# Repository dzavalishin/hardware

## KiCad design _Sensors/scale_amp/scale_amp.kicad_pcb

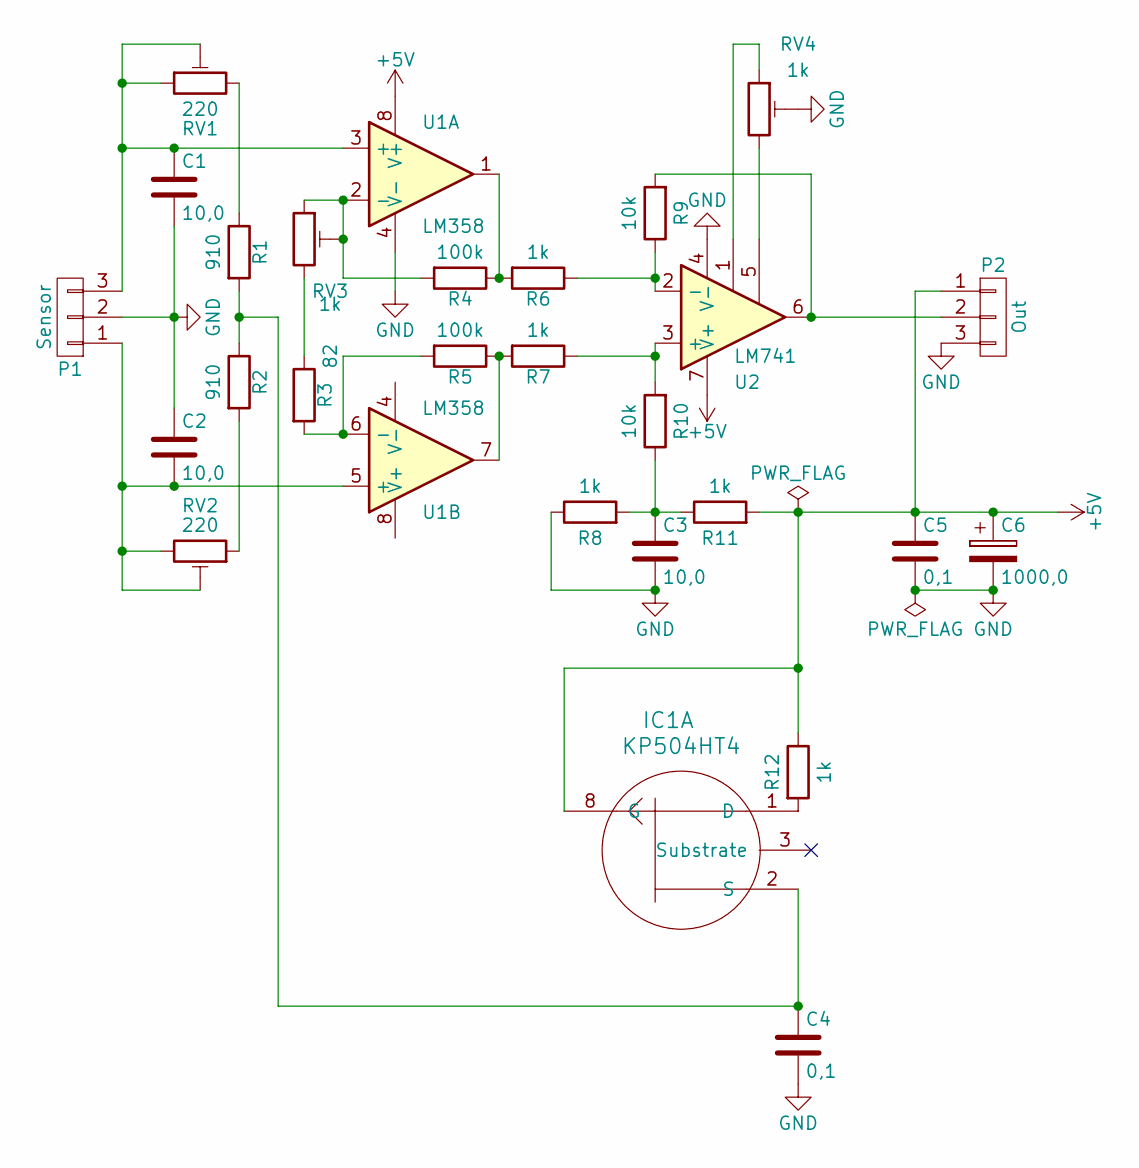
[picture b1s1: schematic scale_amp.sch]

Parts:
C1, C2, C3: 10,0; C_0805_HandSoldering
C4, C5: 0,1; C_1206_HandSoldering
C6: 1000,0; CP_Radial_Tantal_D10.5mm_P5.00mm
IC1: КР504НТ4; DIP-8_W7.62mm_Socket_LongPads
P1: Sensor; PINHEAD1-3
P2: Out; PINHEAD1-3
R1, R2: 910; R_0805_HandSoldering
R3: 82; R_0805_HandSoldering
R4, R5: 100k; R_0805_HandSoldering
R6, R7, R8, R11, R12: 1k; R_0805_HandSoldering
R9, R10: 10k; R_0805_HandSoldering
RV1, RV2: 220; Potentiometer_Trimmer_Suntan_TSR-3386C_Vertical
RV3, RV4: 1k; Potentiometer_Trimmer_Suntan_TSR-3386C_Vertical
U1: LM358; SOIC-8_3.9x4.9mm_Pitch1.27mm
U2: LM741; DIP-8_W7.62mm

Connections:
+5V: C5.1, C6.1, IC1.8 (G), P2.1, R11.2, R12.1, U1.8 (V+), U2.7 (V+)
GND: C1.2, C2.1, C3.2, C4.2, C5.2, C6.2, P1.2, P2.3, R8.1, RV4.2, U1.4 (V-), U2.4 (V-)
unnamed: C1.1, P1.3, RV1.1, RV1.2, U1.3 (+)
unnamed: C2.2, P1.1, RV2.2, RV2.3, U1.5 (+)
unnamed: C3.1, R8.2, R10.1, R11.1
unnamed: C4.1, IC1.2 (S), R1.2, R2.1
unnamed: IC1.1 (D), R12.2
unnamed: P2.2, R9.2, U2.6
unnamed: R1.1, RV1.3
unnamed: R2.2, RV2.1
unnamed: R3.1, RV3.3
unnamed: R3.2, R5.2, U1.6 (-)
unnamed: R4.1, R6.2, U1.1
unnamed: R4.2, RV3.1, RV3.2, U1.2 (-)
unnamed: R5.1, R7.2, U1.7
unnamed: R6.1, R9.1, U2.2 (-)
unnamed: R7.1, R10.2, U2.3 (+)
unnamed: RV4.1, U2.1
unnamed: RV4.3, U2.5

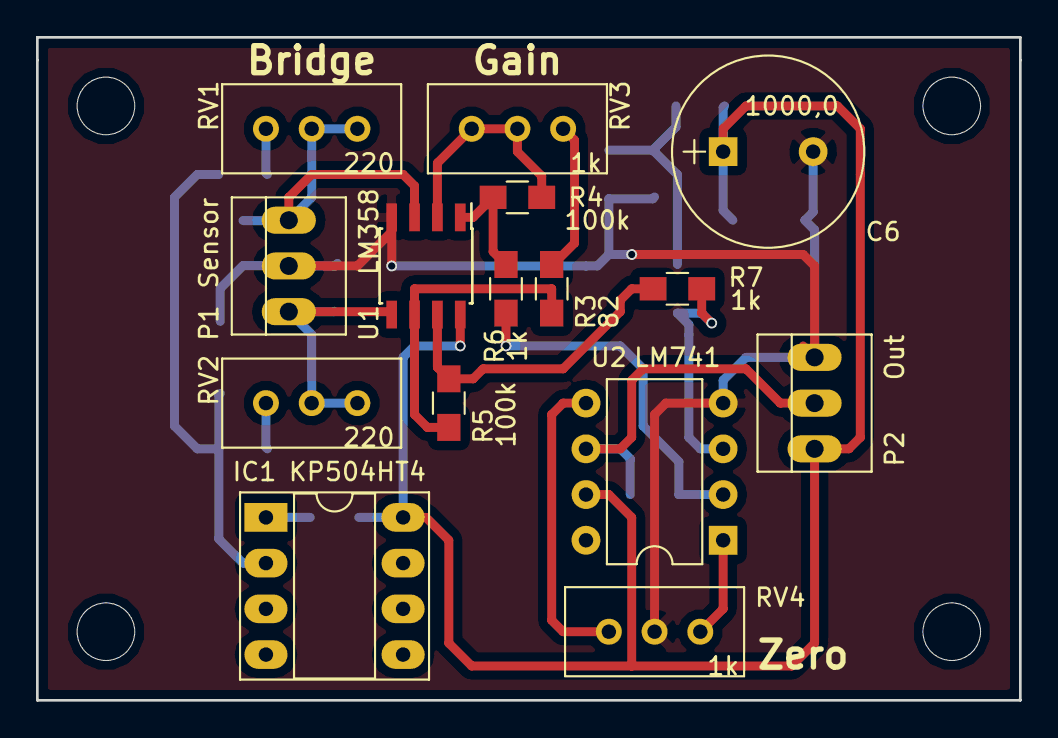
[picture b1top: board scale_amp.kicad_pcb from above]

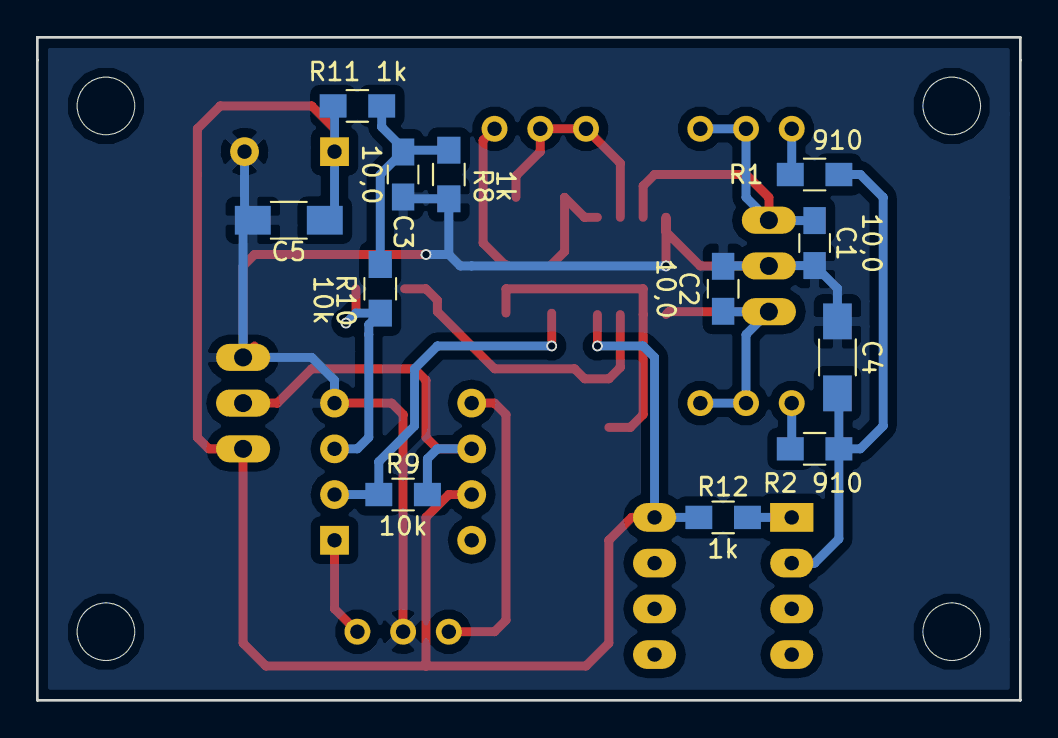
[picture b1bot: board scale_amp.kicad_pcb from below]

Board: 2 copper layers, 54.6 x 36.8 mm, 31 parts (12 on the bottom side), 19 nets.

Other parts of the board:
Hole: Hole; MountingHole_3.2mm_M3
Hole#2, Hole#3, Hole#4: Hole; MountingHole_3.2mm_M3

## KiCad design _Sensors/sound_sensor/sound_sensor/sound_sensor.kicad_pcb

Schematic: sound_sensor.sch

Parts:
C1, C4, C5, C9, C12, C17, C20, C21, C22: 0,1; C_1206_HandSoldering
C2, C16, C19, C23, C24, C27: 100,0; CP_Elec_6.3x5.3
C3, C8, C13, C14, C18: 10,0; C_0805_HandSoldering
C6: 33,0; CP_Elec_6.3x5.3
C7, C15: 470; C_0805_HandSoldering
C10: 0,047; C_0805_HandSoldering
C11: 0,022; C_0805_HandSoldering
C25, C26: 0,33; C_1206_HandSoldering
D1: 157УП2; DIP-14_W7.62mm_Socket_LongPads
D2, D3: 1n4148; D_MiniMELF_Handsoldering
D4: LED_BGRA; LED_Cree-PLCC4_3.2x2.8mm_CCW
J1: OutL; PinHeader_1x02_P2.54mm_Vertical
J2: InL; PinHeader_1x02_P2.54mm_Vertical
J3: InR; PinHeader_1x02_P2.54mm_Vertical
J4: Level; PinHeader_1x02_P2.54mm_Vertical
J5: OutR; PinHeader_1x02_P2.54mm_Vertical
J6: +24; PinHeader_1x02_P2.54mm_Vertical
JP1: Link; SolderJumper-2_P1.3mm_Bridged_Pad1.0x1.5mm
JP2: PwrL; SolderJumper-2_P1.3mm_Open_Pad1.0x1.5mm
JP3: PwrR; SolderJumper-2_P1.3mm_Bridged_Pad1.0x1.5mm
MH1, MH2, MH3, MH4: -; MountingHole_3.2mm_M3
Q1: MMBT3904; SOT-23
R1, R29: 22k; R_1206_HandSoldering
R2, R28: 100k; R_1206_HandSoldering
R3, R11, R18, R27: 47k; R_1206_HandSoldering
R4, R13, R30, R33: 1k; R_1206_HandSoldering
R5, R8, R9, R20, R21, R26: 200k; R_1206_HandSoldering
R6, R19, R23, R24, R25: 20k; R_1206_HandSoldering
R7, R22: 390k; R_1206_HandSoldering
R10, R16: 16k; R_1206_HandSoldering
R12, R15, R17: 100; R_1206_HandSoldering
R14: 10k; R_1206_HandSoldering
R31, R32: 2,2k; R_1206_HandSoldering
R34, R35: 56; R_Axial_DIN0516_L15.5mm_D5.0mm_P20.32mm_Horizontal
RV1, RV2: 1m; Potentiometer_Triwood_RM-065
RV3, RV4: 10k; Potentiometer_Triwood_RM-065
U1: LM2904; DIP-8_W7.62mm_Socket_LongPads
U2: LM2903; DIP-8_W7.62mm_Socket_LongPads
U3: L78L12; TO-92_Inline

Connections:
+12V: C21.1, C22.1, C26.2, C27.1, D4.4, Q1.3 (C), R4.1, R13.1, RV3.1, RV4.3, U1.8, U2.8, U3.1 (VO)
/OutL: C3.2, D1.13, R12.1
/OutR: C18.2, D1.10, R15.2
/PrePwr: C12.1, C13.1, D1.11, Q1.2 (E), R23.2, R24.2, RV1.3, RV2.1
GND: C1.1, C5.2, C6.2, C7.1, C12.2, C13.2, C15.2, C16.2, C20.2, C21.2, C22.2, C23.2, C24.2, C25.2, C26.1, C27.2, D1.4, D1.5, J1.1, J2.2, J3.2, J4.1, J5.1, J6.2, R1.1, R6.1, R11.1, R14.2, R18.2, R19.2, R25.2, R29.2, R32.1, R33.1, RV3.3, RV4.1, U1.4, U2.4, U3.2 (GND)
unnamed: C1.2, R2.1, R3.1
unnamed: C2.1, D1.14, R1.2
unnamed: C2.2, R2.2
unnamed: C3.1, J1.2
unnamed: C4.1, R3.2, R5.2
unnamed: C4.2, D1.2, R7.1
unnamed: C5.1, C6.1, R4.2, R10.1, R33.2
unnamed: C7.2, C8.1, D1.3, R7.2, R11.2
unnamed: C8.2, J2.1, JP1.2, JP2.1
unnamed: C9.1, R16.2, U1.1, U1.2
unnamed: C9.2, R14.1, U1.5
unnamed: C10.1, C11.2, R16.1
unnamed: C10.2, R12.2, R15.1
unnamed: C11.1, R10.2, U1.3
unnamed: C14.1, C15.1, D1.6, R18.1, R22.2
unnamed: C14.2, J3.1, JP1.1, JP3.2
unnamed: C16.1, D2.1, R17.2, R19.1, U1.6, U2.2, U2.6
unnamed: C17.1, D1.7, R22.1
unnamed: C17.2, R26.1, R27.1
unnamed: C18.1, J5.2
unnamed: C19.1, D1.9, R29.1
unnamed: C19.2, R28.2
unnamed: C20.1, R27.2, R28.1
unnamed: C23.1, Q1.1 (B), R13.2
unnamed: C24.1, C25.1, R35.1, U3.3 (VI)
unnamed: D1.1, R5.1, R8.1
unnamed: D1.8, R20.1, R26.2
unnamed: D2.2, U1.7
unnamed: D3.1, R34.1
unnamed: D3.2, J6.1
unnamed: D4.1, R31.1
unnamed: D4.2, R30.1
unnamed: D4.3, R32.2
unnamed: J4.2, R17.1
unnamed: JP2.2, R23.1
unnamed: JP3.1, R24.1
unnamed: R6.2, R8.2, R9.1
unnamed: R9.2, RV1.1, RV1.2
unnamed: R20.2, R21.1, R25.1
unnamed: R21.2, RV2.2, RV2.3
unnamed: R30.2, U2.1
unnamed: R31.2, U2.7
unnamed: R34.2, R35.2
unnamed: RV3.2, U2.3
unnamed: RV4.2, U2.5

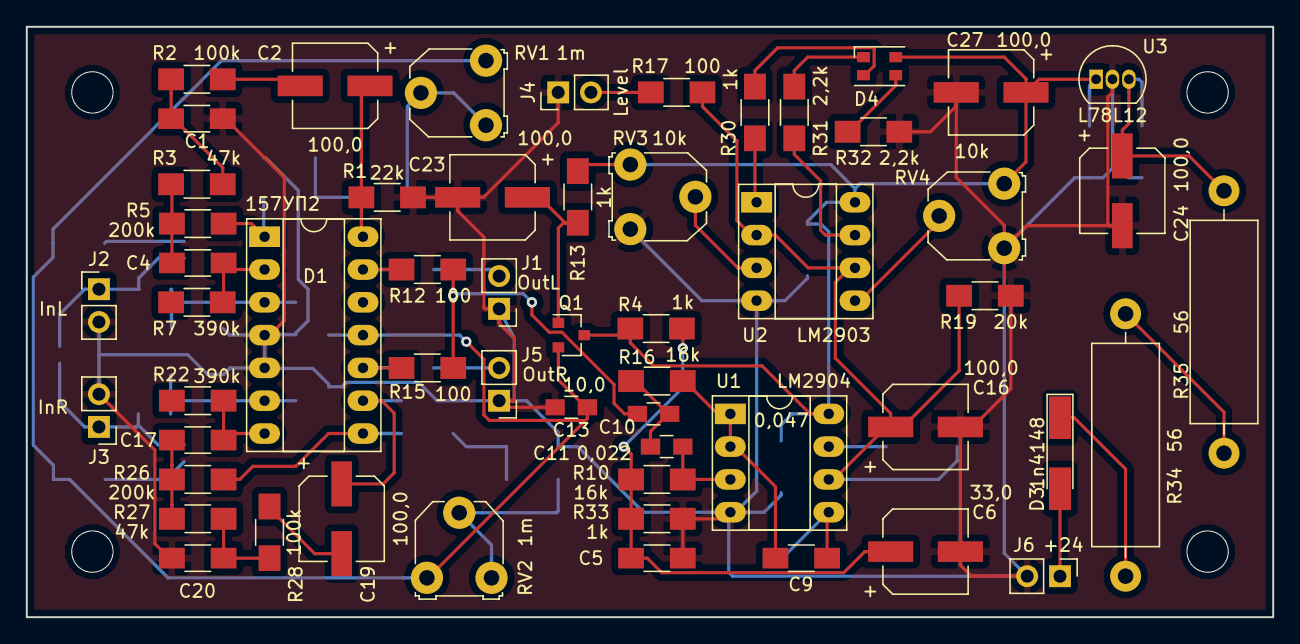
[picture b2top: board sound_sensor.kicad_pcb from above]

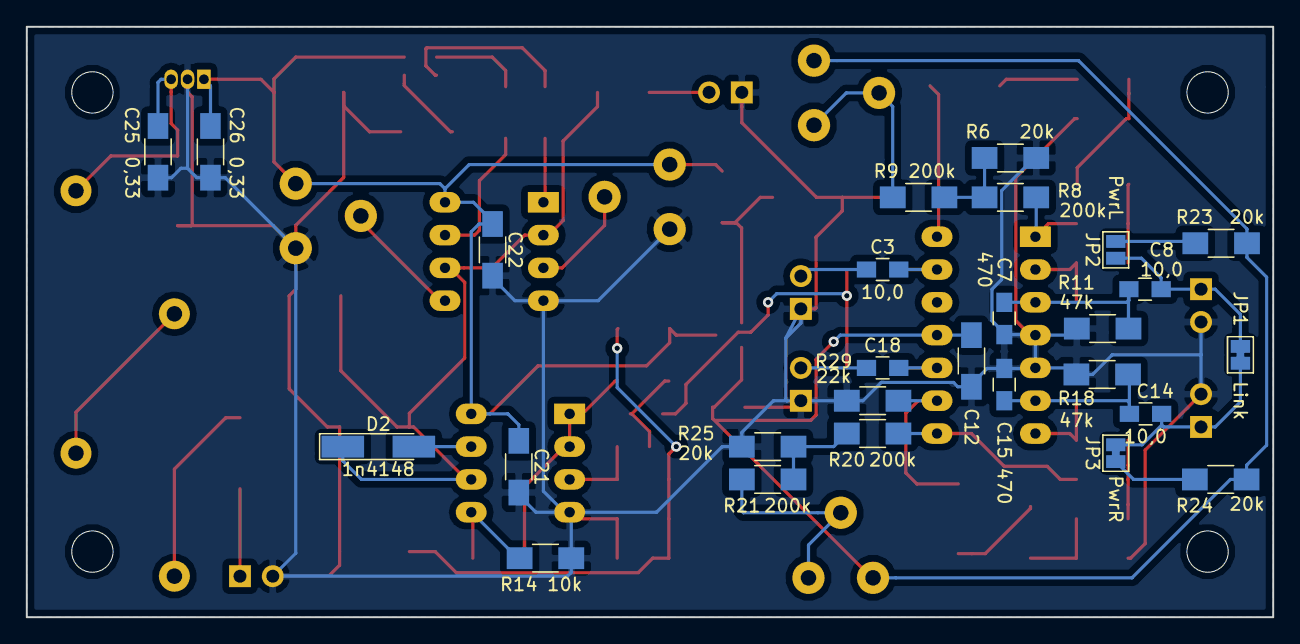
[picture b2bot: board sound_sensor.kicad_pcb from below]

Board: 2 copper layers, 96.5 x 45.7 mm, 87 parts (27 on the bottom side), 50 nets.

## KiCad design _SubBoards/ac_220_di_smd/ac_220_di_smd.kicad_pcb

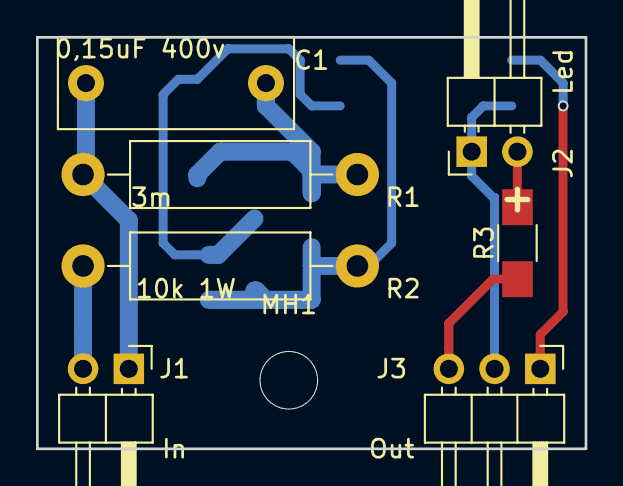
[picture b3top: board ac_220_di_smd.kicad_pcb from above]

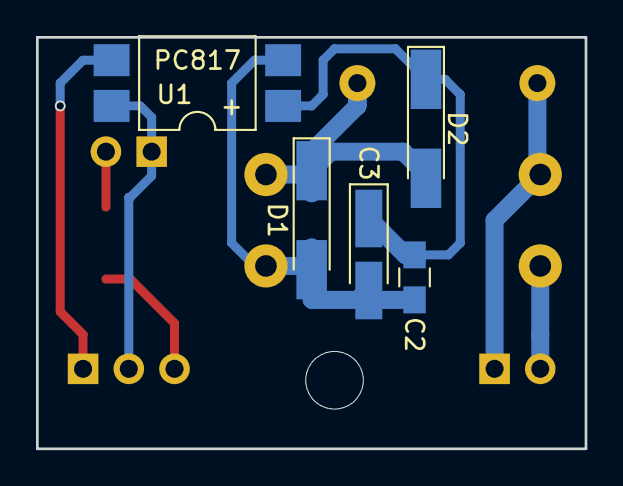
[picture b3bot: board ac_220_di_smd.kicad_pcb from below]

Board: 2 copper layers, 30.5 x 22.9 mm, 13 parts (5 on the bottom side), 9 nets.

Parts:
C1: 0,15uF 400v; C_Rect_L13.0mm_W5.0mm_P10.00mm_FKS3_FKP3_MKS4
C2: 0,1; C_0805_HandSoldering
C3: 10,0; CP_Tantalum_Case-A_EIA-3216-18_Hand
D1, D2: 4448; D_MiniMELF_Handsoldering
J1: In; Pin_Header_Angled_1x02_Pitch2.54mm
J2: Led; Pin_Header_Angled_1x02_Pitch2.54mm
J3: Out; Pin_Header_Angled_1x03_Pitch2.54mm
MH1: MountingHole; MountingHole_3.2mm_M3
R1: 3m; R_Axial_DIN0411_L9.9mm_D3.6mm_P15.24mm_Horizontal
R2: 10k 1W; R_Axial_DIN0411_L9.9mm_D3.6mm_P15.24mm_Horizontal
R3: 4,7k; R_1206_HandSoldering
U1: PC817; SMDIP-4_W9.53mm

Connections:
unnamed: C1.1, D1.1, D2.2, R1.1
unnamed: C1.2, J1.1, R1.2
unnamed: C2.1, C3.2, D1.2, R2.1, U1.2
unnamed: C2.2, C3.1, D2.1, U1.1
unnamed: J1.2, R2.2
unnamed: J2.1, J3.2, U1.4
unnamed: J2.2, R3.2
unnamed: J3.1, U1.3
unnamed: J3.3, R3.1

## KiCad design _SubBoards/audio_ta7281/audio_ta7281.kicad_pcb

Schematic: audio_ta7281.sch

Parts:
C1, C8, C9, C12: 100,0; CP_Radial_D6.3mm_P2.50mm
C2, C4: 1,0; CP_Radial_D5.0mm_P2.00mm
C3: 1n; C_1206_HandSoldering
C5: 47,0; CP_Radial_D8.0mm_P5.00mm
C6: 1000,0; CP_Radial_D12.5mm_P5.00mm
C7, C10: 0,1; C_1206_HandSoldering
C11, C14: 0,22; C_Disc_D4.3mm_W1.9mm_P5.00mm
C13: 0,15; C_Disc_D8.0mm_W5.0mm_P10.00mm
J1: PwrA; TerminalBlock_Pheonix_MKDS1.5-2pol
J2: PwrB; TerminalBlock_Pheonix_MKDS1.5-2pol
J3: Out; TerminalBlock_Pheonix_MKDS1.5-2pol
P1: In; PINHEAD1-2
R1, R2: 430; R_1206_HandSoldering
R3: 1; R_Axial_DIN0922_L20.0mm_D9.0mm_P30.48mm_Horizontal
R4: 2k; R_1206_HandSoldering
R5: 43; R_1206_HandSoldering
U1: TA7281; HZIP12-P-1.78B

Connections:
/In: C2.2, P1.2
/OutA: C8.2, C14.1, J3.2, R3.1, R4.1, U1.1
/OutB: C9.2, C11.2, C13.2, J3.1, U1.6
/Power: C6.1, C7.2, C11.1, J1.2, J2.2, U1.3
GNDA: C1.2, C4.2, C5.2, C6.2, C7.1, C10.2, C14.2, J1.1, J2.1, P1.1, R5.2, U1.4, U1.10
unnamed: C1.1, R1.2
unnamed: C2.1, C3.1, U1.12
unnamed: C3.2, R1.1, U1.11
unnamed: C4.1, U1.8
unnamed: C5.1, U1.7
unnamed: C8.1, U1.2
unnamed: C9.1, U1.5
unnamed: C10.1, C12.1, U1.9
unnamed: C12.2, R2.2
unnamed: C13.1, R3.2
unnamed: R2.1, R4.2, R5.1

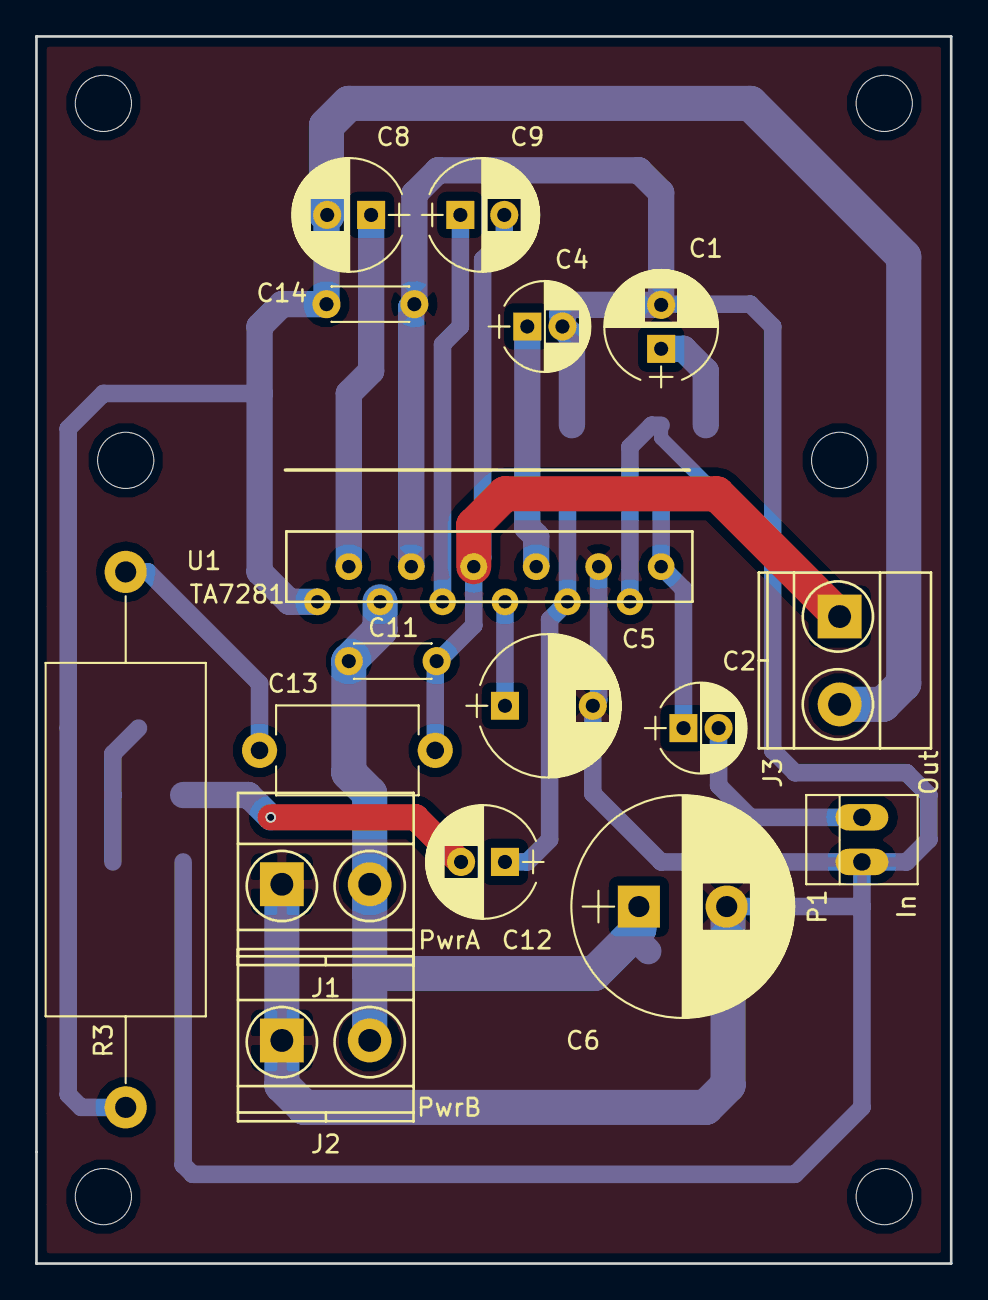
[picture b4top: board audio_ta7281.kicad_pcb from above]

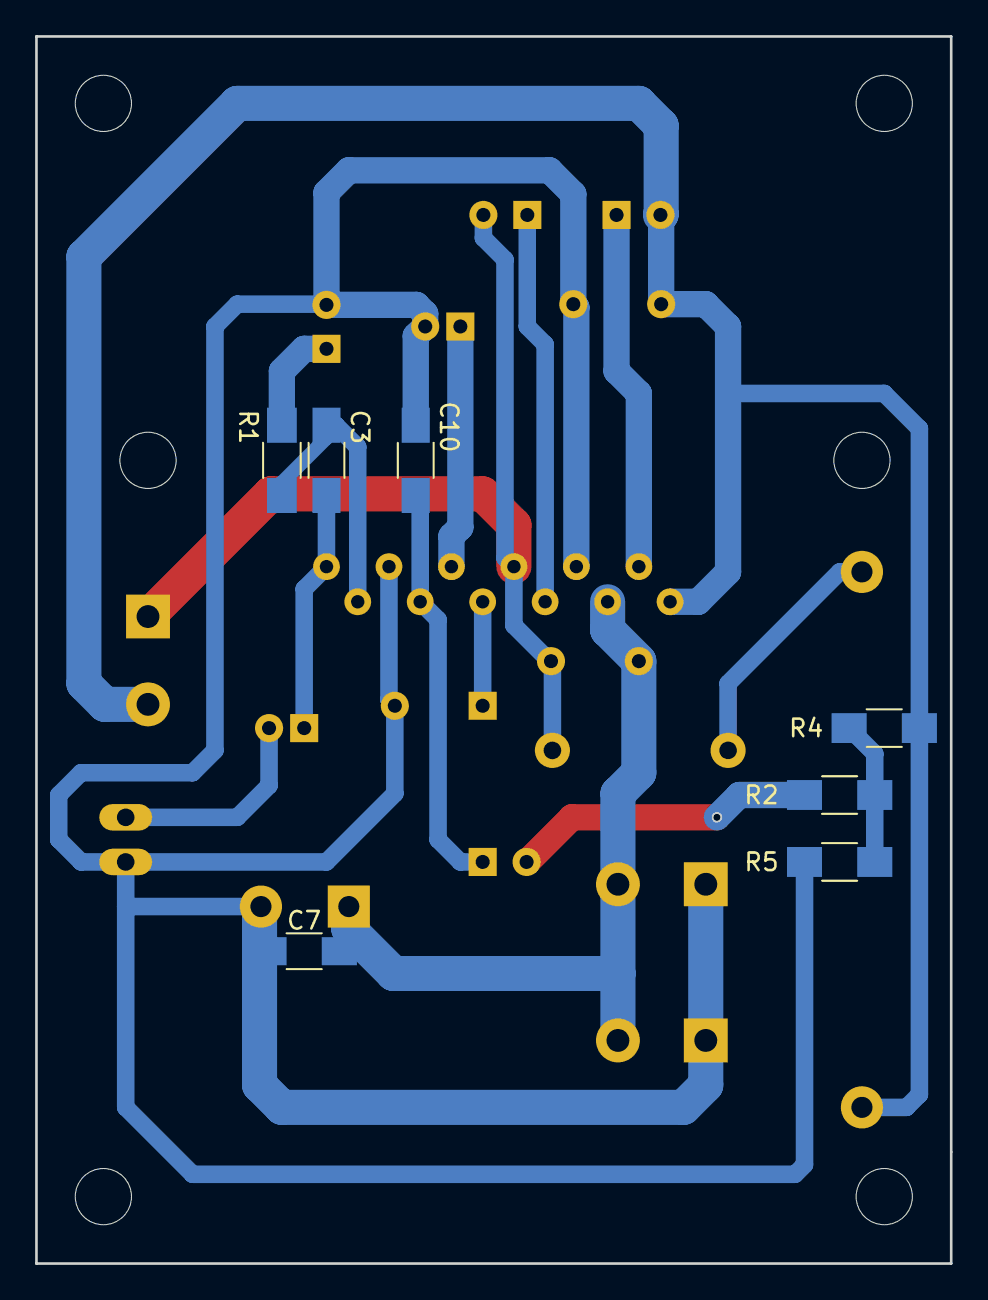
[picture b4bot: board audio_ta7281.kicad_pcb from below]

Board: 2 copper layers, 52.1 x 69.8 mm, 24 parts (7 on the bottom side), 16 nets.

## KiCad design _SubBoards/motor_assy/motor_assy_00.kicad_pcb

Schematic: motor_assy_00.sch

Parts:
C1, C9, C14: 47,0; CP_Elec_6.3x5.3
C2, C5, C7, C8, C10, C11, C12, C13: 0,1; C_1206_HandSoldering
C3: 1,0; C_1206_HandSoldering
C4, C6: 100,0; CP_Elec_6.3x5.3
D1: L293D; DIP-16_W7.62mm_Socket_LongPads
D2, D3, D4, D5, D6, D7, D8, D9, D11: D; D_MiniMELF_Handsoldering
D10: 15v0; D_MiniMELF_Handsoldering
J1: Ai_Ext; TerminalBlock_Pheonix_MKDS1.5-2pol
L1: 100mH; Choke_Toroid_8x16mm_Vertical
P1: Control; Socket_Strip_Angled_1x07
P2: Motor1; Socket_Strip_Angled_1x02
P3: Motor2; Socket_Strip_Angled_1x02
P4: +5/Sense; Socket_Strip_Angled_1x04
P5: +12; Socket_Strip_Angled_1x02
Q1: 2N3904; TO-92_Molded_Narrow
R1, R2: 10k; R_1206_HandSoldering
R3, R4: 100k; R_1206_HandSoldering
R5: 0,2; R_Axial_DIN0414_L11.9mm_D4.5mm_P15.24mm_Horizontal
R6, R7: 200; R_1206_HandSoldering
R8: 2k; R_1206_HandSoldering
R9: 1M; R_1206_HandSoldering
R10: 1k; R_1206_HandSoldering
R11: 100; R_1206_HandSoldering
U1: TL082; DIP-8_W7.62mm_Socket_LongPads
U2: L78L05; TO-92_Inline_Narrow_Oval

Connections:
+5V: C13.1, C14.2, D1.16 (VccDig), P4.2, R1.2, R2.2, U2.1 (VO)
+12V: C7.2, C9.1, C12.1, D10.1, R11.1, U1.8 (V+), U2.3 (VI)
/+12Motor: C4.1, C5.1, L1.2, R5.1, R6.2
/A1: D1.2 (A), P1.2
/A2: D1.10 (A), P1.6, R4.2
/Ai_Ext: P4.4, U1.6 (-), U1.7
/Ai_I_Sense: C3.1, P4.3, Q1.3, R8.1
/B1: D1.7 (B), P1.3
/B2: D1.15 (B), P1.5, R3.2
/En1: D1.1 (En), P1.1, R1.1
/En2: D1.9 (En), P1.7, R2.1
/MPower: C1.1, C2.1, D1.8 (Pwr), D2.1, D4.1, D6.1, D8.1, R5.2, R7.2
GND: C1.2, C2.2, C3.2, C4.2, C5.2, C6.2, C7.1, C8.2, C9.2, C12.2, C13.2, C14.1, D1.4 (Gnd), D1.5 (Gnd), D1.12 (Gnd), D1.13 (Gnd), D3.2, D5.2, D7.2, D9.2, D10.2, J1.2, P1.4, P4.1, P5.2, R3.1, R4.1, R8.2, R9.1, U1.4 (V-), U2.2 (GND)
unnamed: C6.1, C8.1, D11.1, L1.1, R11.2
unnamed: C10.1, D1.3 (OA), D2.2, D3.1, P2.1
unnamed: C10.2, D1.6 (OB), D6.2, D7.1, P2.2
unnamed: C11.1, D1.11 (OA), D4.2, D5.1, P3.1
unnamed: C11.2, D1.14 (OB), D8.2, D9.1, P3.2
unnamed: D11.2, P5.1
unnamed: J1.1, R9.2, R10.2
unnamed: Q1.1, R6.1, U1.3 (+)
unnamed: Q1.2, U1.1
unnamed: R7.1, U1.2 (-)
unnamed: R10.1, U1.5 (+)

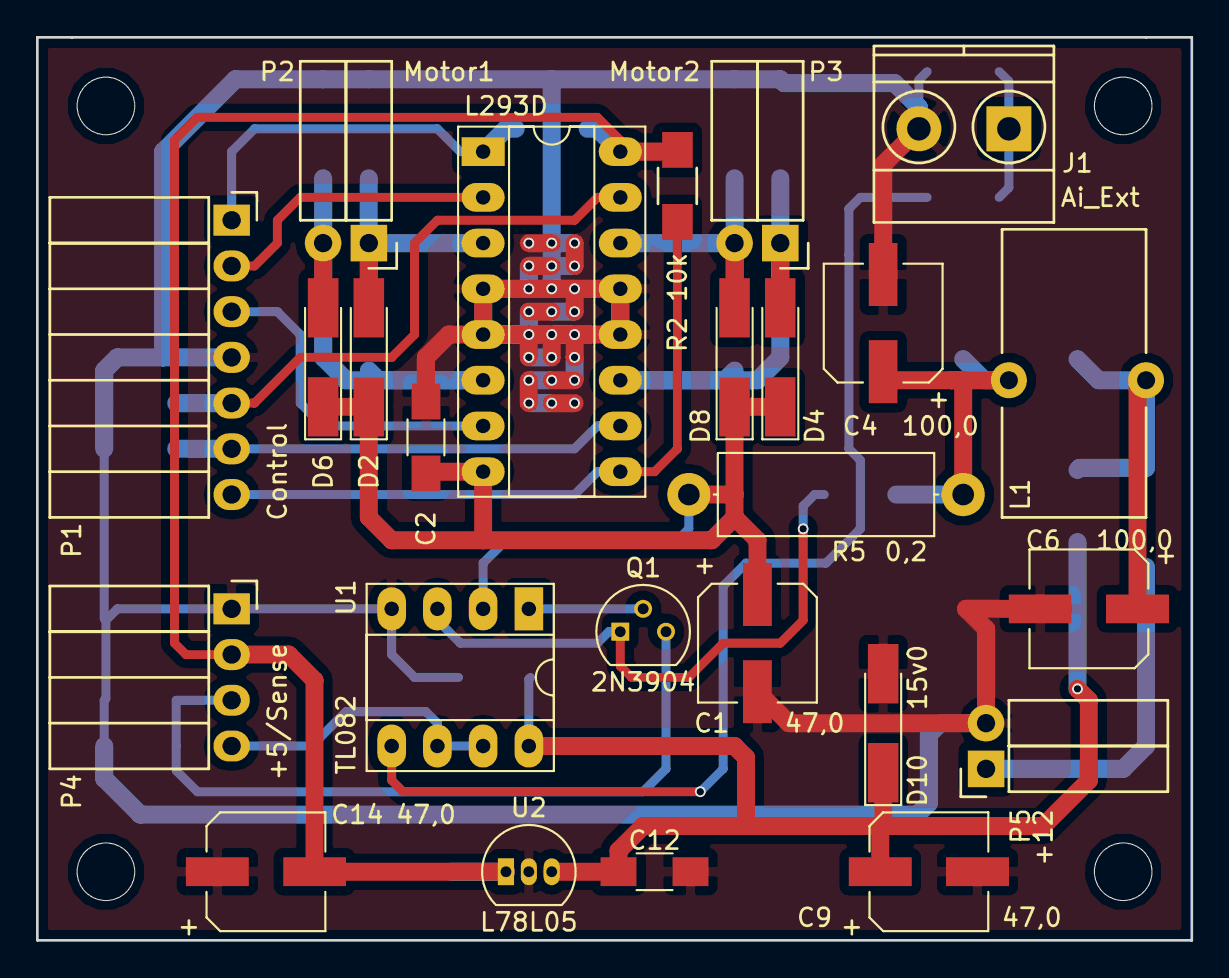
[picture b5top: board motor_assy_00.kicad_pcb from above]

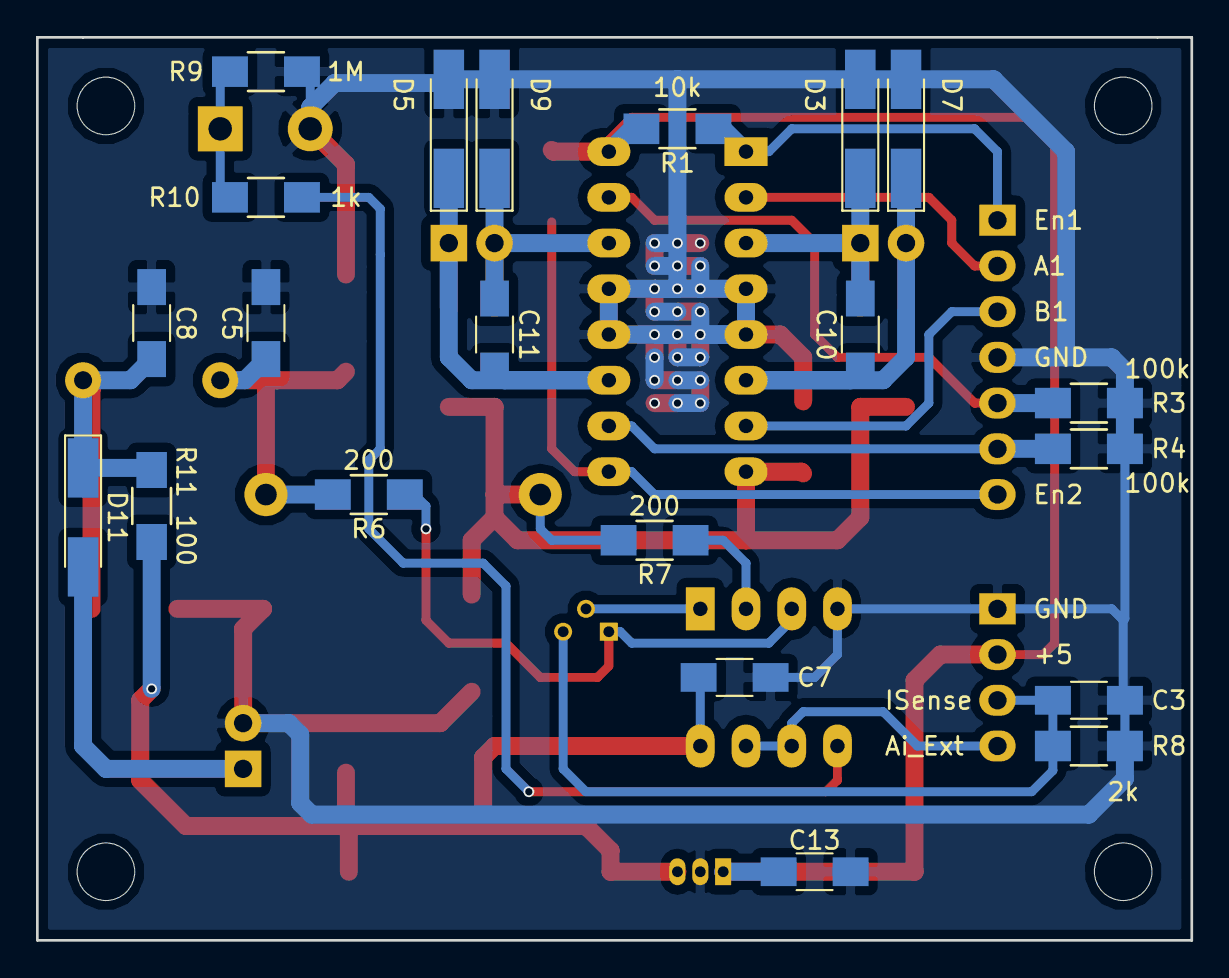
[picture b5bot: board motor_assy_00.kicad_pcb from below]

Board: 2 copper layers, 64.1 x 50.2 mm, 50 parts (21 on the bottom side), 24 nets.

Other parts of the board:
hole: MountingHole_3.2mm_M3
hole#2, hole#3, hole#4: MountingHole_3.2mm_M3

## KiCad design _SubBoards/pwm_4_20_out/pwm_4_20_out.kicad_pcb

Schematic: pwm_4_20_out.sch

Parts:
C1, C2: 10,0; C_0805_HandSoldering
IC1: КР504НТ4; DIP-8_W7.62mm_LongPads
J1, J3: Out 4-20 mA; TerminalBlock_bornier-2_P5.08mm
J2: PWM; Pin_Header_Angled_1x04_Pitch2.54mm
R1, R2: 560; R_0805_HandSoldering
R3, R4: 18; R_0805_HandSoldering
RV1, RV2: 50R; Potentiometer_Trimmer_Bourns_3296W
U1, U2: LTV-817; SOP-4_3.8x4.1mm_Pitch2.54mm

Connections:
unnamed: C1.1, IC1.8, J1.2, RV1.2, RV1.3
unnamed: C1.2, J1.1, U1.3
unnamed: C2.1, IC1.6, J3.2, RV2.2, RV2.3
unnamed: C2.2, J3.1, U2.3
unnamed: IC1.1, R3.2
unnamed: IC1.2, U1.4
unnamed: IC1.4, R4.2
unnamed: IC1.5, U2.4
unnamed: J2.1, U2.2
unnamed: J2.2, R2.2
unnamed: J2.3, U1.2
unnamed: J2.4, R1.2
unnamed: R1.1, U1.1
unnamed: R2.1, U2.1
unnamed: R3.1, RV1.1
unnamed: R4.1, RV2.1

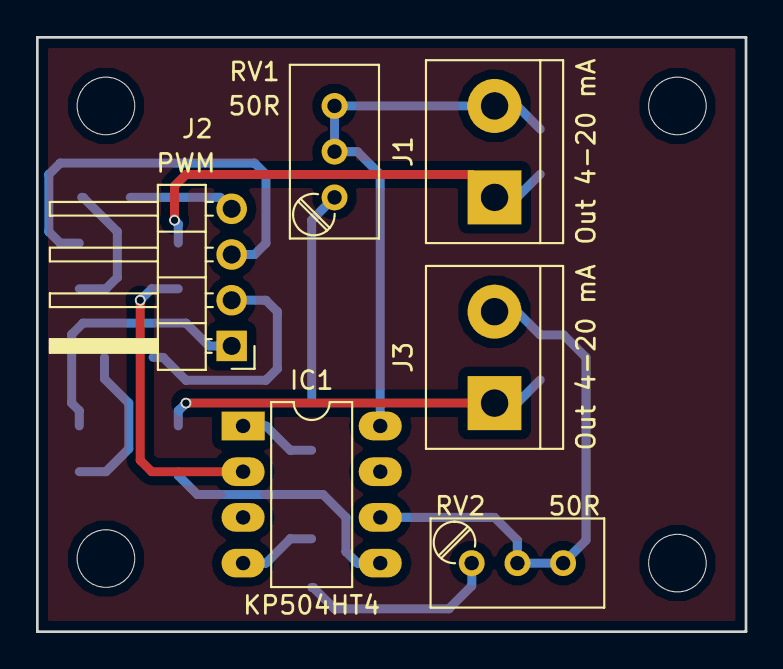
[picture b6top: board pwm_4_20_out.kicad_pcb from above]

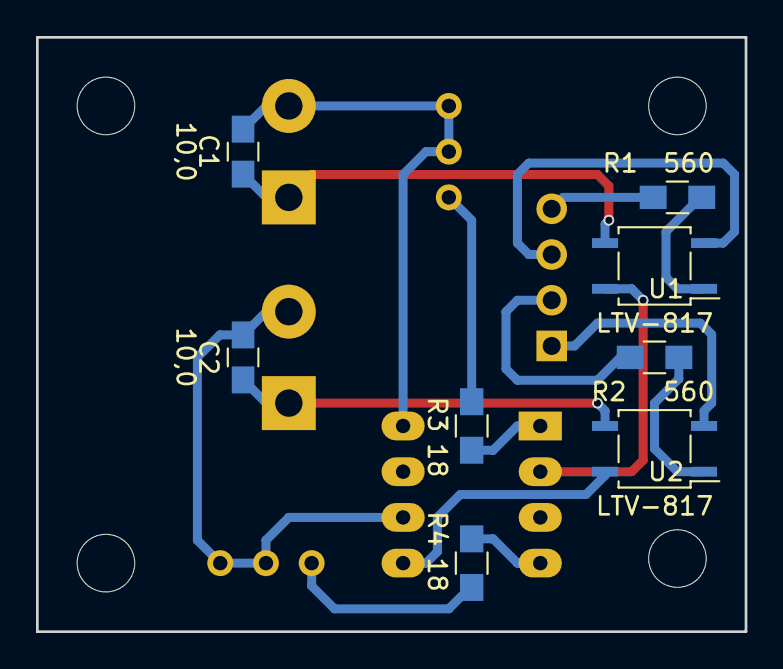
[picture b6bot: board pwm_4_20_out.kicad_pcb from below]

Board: 2 copper layers, 39.4 x 33.0 mm, 18 parts (8 on the bottom side), 16 nets.

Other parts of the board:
hole: MountingHole_3.2mm_M3
hole#2, hole#3, hole#4: MountingHole_3.2mm_M3

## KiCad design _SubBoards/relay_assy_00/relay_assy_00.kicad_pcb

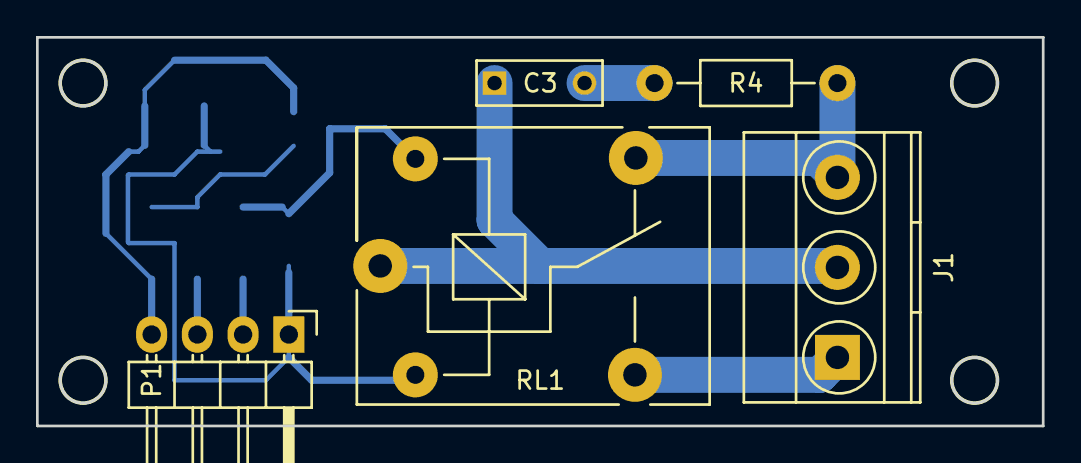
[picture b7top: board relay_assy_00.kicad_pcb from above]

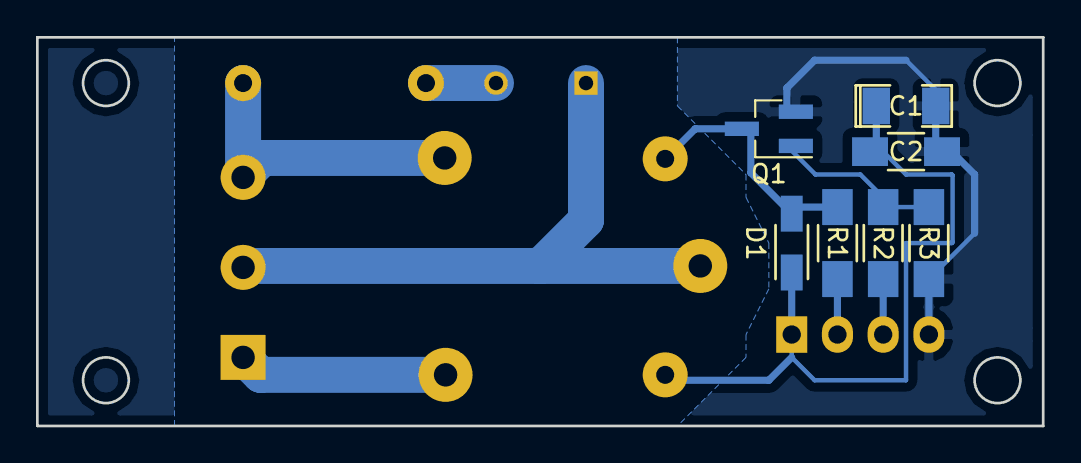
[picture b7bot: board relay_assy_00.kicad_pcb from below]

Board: 2 copper layers, 55.9 x 21.6 mm, 12 parts (7 on the bottom side), 10 nets.

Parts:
C1: 10,0; SMD-1206_Pol
C2: 0,1; C_1206_HandSoldering
C3: 0,022; C_Rect_L7_W2.5_P5
D1: 1N4148W; SOD-123
J1: Screw_Terminal_1x03; TerminalBlock_Pheonix_MKDS1.5-3pol
P1: CONN_01X04; Pin_Header_Angled_1x04
Q1: BC817-40; SOT-23_Handsoldering
R1: 1k; R_1206_HandSoldering
R2: 560; R_1206_HandSoldering
R3: 10k; R_1206_HandSoldering
R4: 56; Resistor_Horizontal_RM10mm
RL1: RM50-xx11; Relay_SANYOU_SRD_Series_Form_C

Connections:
GND: C1.2, C2.2, P1.4, Q1.2, R3.2
unnamed: C1.1, C2.1, D1.1, P1.1, RL1.2
unnamed: C3.1, J1.2, RL1.1
unnamed: C3.2, R4.1
unnamed: D1.2, Q1.3, R1.1, RL1.5
unnamed: J1.1, RL1.3
unnamed: J1.3, R4.2, RL1.4
unnamed: P1.3, R2.2
unnamed: Q1.1, R2.1, R3.1
unnamed: P1.2, R1.2
